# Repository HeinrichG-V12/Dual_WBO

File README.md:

# Dual channel wideband oxygen controller

## Development status

- Hardware: working in progress, check hardware/V0.0.1 for actual status
- Software: not started yet

### Dual WBO controller based on

- Microchip AT90CAN128
- 2x Bosch CJ125 wideband lambda controller
- NXP TJA1050T high speed can transceiver
- Infineon TLE42754D LDO 5v and 450mA
- Analog Devices AD5337 8-bit DAC
- Analog Devices ADR02 5v and 10mA precision reference (0.1%) for TLS115
- Infineon TLS115B0EJ voltage tracker for analog part, provides 5v and 150mA
- ...

### Features

- supports **LSU4.9** probes only
- Automotive grade components
- 2x LSU 4.9 connector (TE 1813139-1)
- 4 layer PCB
- integrated with TunerStudio

### Inputs

- 2x LSU4.9 probes
- CAN HS with up to 1mbit/s
- UART for configuration
- UBat input for activation the controller

### Outputs

- dual analog output, either as 0..5V for Lambda 0.65 to 1.35 **OR** narrow band emulation
- CAN output (AEM X-Series protocol) for both channels and debug messages

### Bosch CJ125 (LQFP32 package) part numbers

|Bosch part number|
|:----------------|
|30615|
|40103|
|30522|

#### A couple of CJ125 ICs

### Suitable Bosch lambda probes

Basically, the Bosch probes whose numbers start with **0 258 017** will fit, also Bosch **0 281 004**.  
Bosch numbers beginning with **0 258 007** are *LSU 4.2* probes and will not fit.

|Bosch number  |Length overall|Comment|
|--------------|--------------|-------|
|0 258 017 012 |1060mm||
|0 258 017 025 |1000mm|Bosch motorsport part|
|0 258 017 029 |620mm|grey, used by BMW after 09/2006 (1178 7539124)|
|0 258 017 038 |340mm|grey, used by BMW (11787537984)|
|0 258 017 092 |950mm|black, used by BMW (1178 7540167)|
|0 258 017 126 |680mm|black, used by BMW after 09/2006 (1178 7561410)|
|0 281 004 028 |540mm||
|0 281 004 150 |1215mm||
|0 281 004 184 |1000mm||
|...|||

### LSU4.9 probe pinout

|Pin#|Color|Description|Symbol|
|----|-----|--------|-----------|
|1|red|Pump current APE|IP|
|2|yellow|Virtual ground IPN|VM|
|3|white|Heater voltage H-|Uh-|
|4|grey|Heater voltaget H+|Uh+|
|5|green|Trim Resistor RT|IA|
|6|black|Nernst voltage UN|RE|

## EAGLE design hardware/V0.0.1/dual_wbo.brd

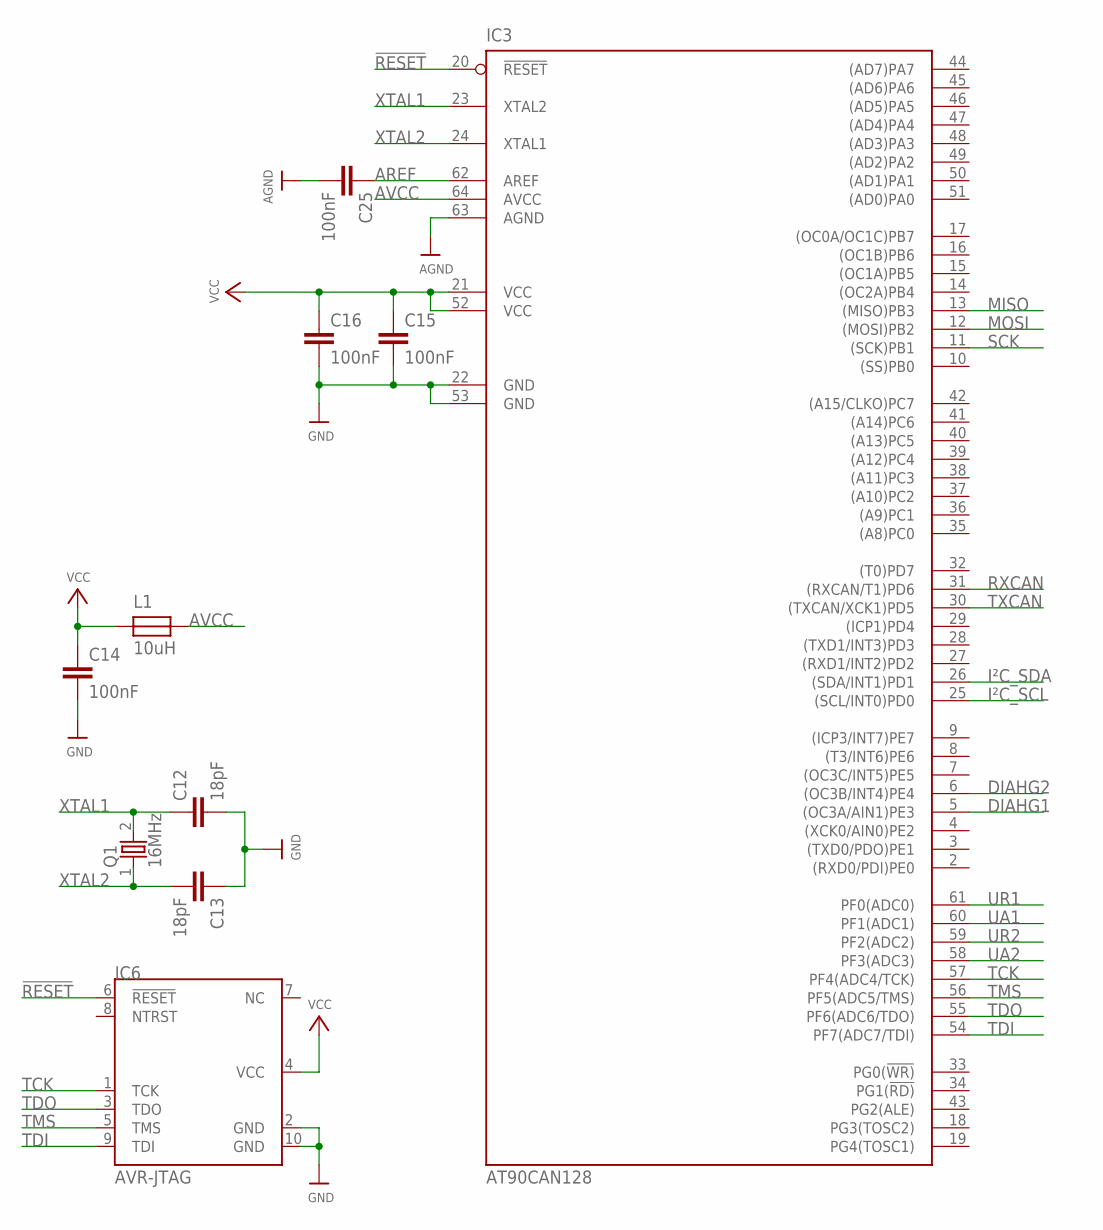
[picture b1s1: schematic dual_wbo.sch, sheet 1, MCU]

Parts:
C12, C13: 18pF; C0603
C14, C15, C16, C25: 100nF; C0603
IC3: AT90CAN128; TQFP64
IC6: AVR-JTAG; 2X05_1.27MM_SMT
L1: 10uH; R0603
Q1: 16MHz; ABM3

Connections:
!RESET: IC3.20 (!RESET), IC6.6 (!RESET)
AGND: C25.2, IC3.63 (AGND); also elsewhere on the board
AREF: C25.1, IC3.62 (AREF); also elsewhere on the board
AVCC: IC3.64 (AVCC), L1.2
DIAHG1: IC3.5 ((OC3A/AIN1)PE3); also elsewhere on the board
DIAHG2: IC3.6 ((OC3B/INT4)PE4); also elsewhere on the board
GND: C12.2, C13.1, C14.2, C15.2, C16.2, IC3.22 (GND), IC3.53 (GND), IC6.2 (GND), IC6.10 (GND); also elsewhere on the board
I²C_SCL: IC3.25 ((SCL/INT0)PD0); also elsewhere on the board
I²C_SDA: IC3.26 ((SDA/INT1)PD1); also elsewhere on the board
MISO: IC3.13 ((MISO)PB3); also elsewhere on the board
MOSI: IC3.12 ((MOSI)PB2); also elsewhere on the board
RXCAN: IC3.31 ((RXCAN/T1)PD6); also elsewhere on the board
SCK: IC3.11 ((SCK)PB1); also elsewhere on the board
TCK: IC3.57 (PF4(ADC4/TCK)), IC6.1 (TCK)
TDI: IC3.54 (PF7(ADC7/TDI)), IC6.9 (TDI)
TDO: IC3.55 (PF6(ADC6/TDO)), IC6.3 (TDO)
TMS: IC3.56 (PF5(ADC5/TMS)), IC6.5 (TMS)
TXCAN: IC3.30 ((TXCAN/XCK1)PD5); also elsewhere on the board
UA1: IC3.60 (PF1(ADC1)); also elsewhere on the board
UA2: IC3.58 (PF3(ADC3)); also elsewhere on the board
UR1: IC3.61 (PF0(ADC0)); also elsewhere on the board
UR2: IC3.59 (PF2(ADC2)); also elsewhere on the board
VCC: C14.1, C15.1, C16.1, IC3.21 (VCC), IC3.52 (VCC), IC6.4 (VCC), L1.1; also elsewhere on the board
XTAL1: C12.1, IC3.23 (XTAL2), Q1.2
XTAL2: C13.2, IC3.24 (XTAL1), Q1.1

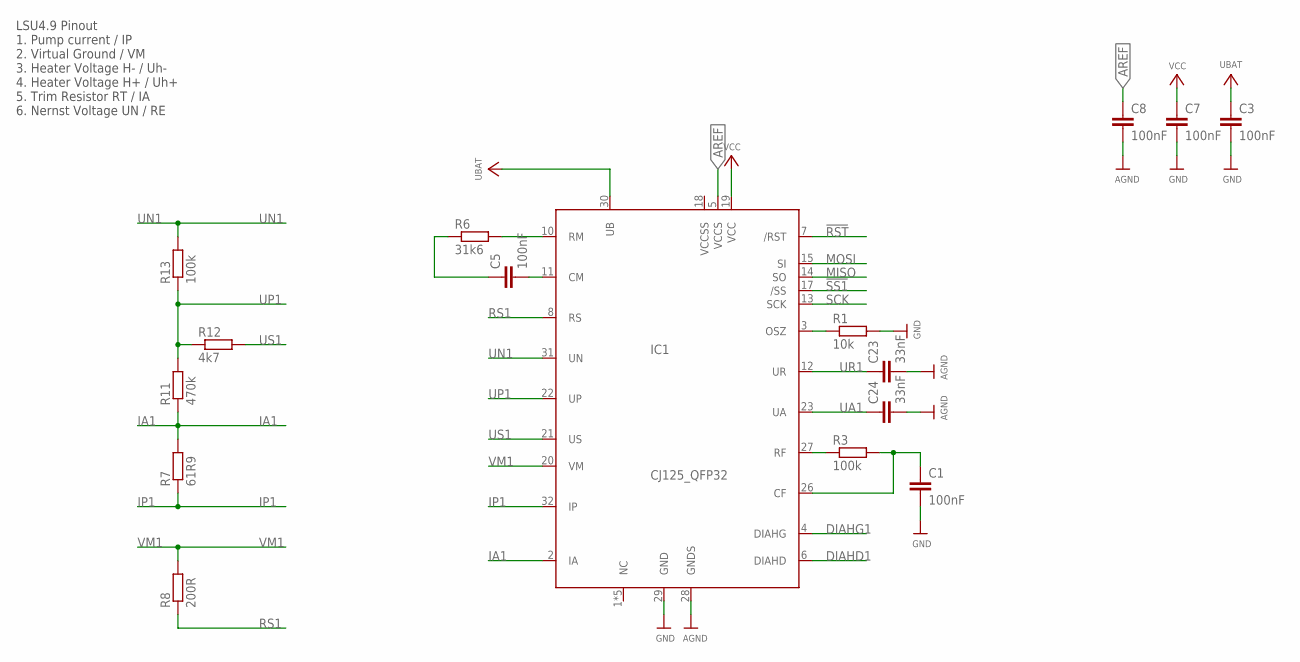
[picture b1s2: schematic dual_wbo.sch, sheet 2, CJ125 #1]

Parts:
C1, C3, C5, C7, C8: 100nF; C0603
C23, C24: 33nF; C0603
IC1: CJ125_QFP32; TQFP32-08
R1: 10k; R0603
R3, R13: 100k; R0603
R6: 31k6; R0603
R7: 61R9; R0603
R8: 200R; R0603
R11: 470k; R0603
R12: 4k7; R0603

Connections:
!RST: IC1.7 (/RST); also elsewhere on the board
!SS1: IC1.17 (/SS)
+UBAT: C3.1, IC1.30 (UB); also elsewhere on the board
AGND: C8.2, C23.2, C24.2, IC1.28 (GNDS); also elsewhere on the board
AREF: C8.1, IC1.5 (VCCS); also elsewhere on the board
DIAHD1: IC1.6 (DIAHD); also elsewhere on the board
DIAHG1: IC1.4 (DIAHG); also elsewhere on the board
GND: C1.2, C3.2, C7.2, IC1.29 (GND), R1.2; also elsewhere on the board
IA1: IC1.2 (IA), R7.2, R11.1
IP1: IC1.32 (IP), R7.1
MISO: IC1.14 (SO); also elsewhere on the board
MOSI: IC1.15 (SI); also elsewhere on the board
unnamed: IC1.3 (OSZ), R1.1
unnamed: IC1.27 (RF), R3.1
unnamed: C1.1, IC1.26 (CF), R3.2
unnamed: IC1.10 (RM), R6.2
unnamed: C5.1, R6.1
unnamed: C5.2, IC1.11 (CM)
RS1: IC1.8 (RS), R8.1
SCK: IC1.13 (SCK); also elsewhere on the board
UA1: C24.1, IC1.23 (UA); also elsewhere on the board
UN1: IC1.31 (UN), R13.2
UP1: IC1.22 (UP), R11.2, R12.1, R13.1
UR1: C23.1, IC1.12 (UR); also elsewhere on the board
US1: IC1.21 (US), R12.2
VCC: C7.1, IC1.19 (VCC); also elsewhere on the board
VM1: IC1.20 (VM), R8.2

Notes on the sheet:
LSU4.9 Pinout 1. Pump current / IP 2. Virtual Ground / VM 3. Heater Voltage H- / Uh- 4. Heater Voltage H+ / Uh+ 5. Trim Resistor RT / IA 6. Nernst Voltage UN / RE

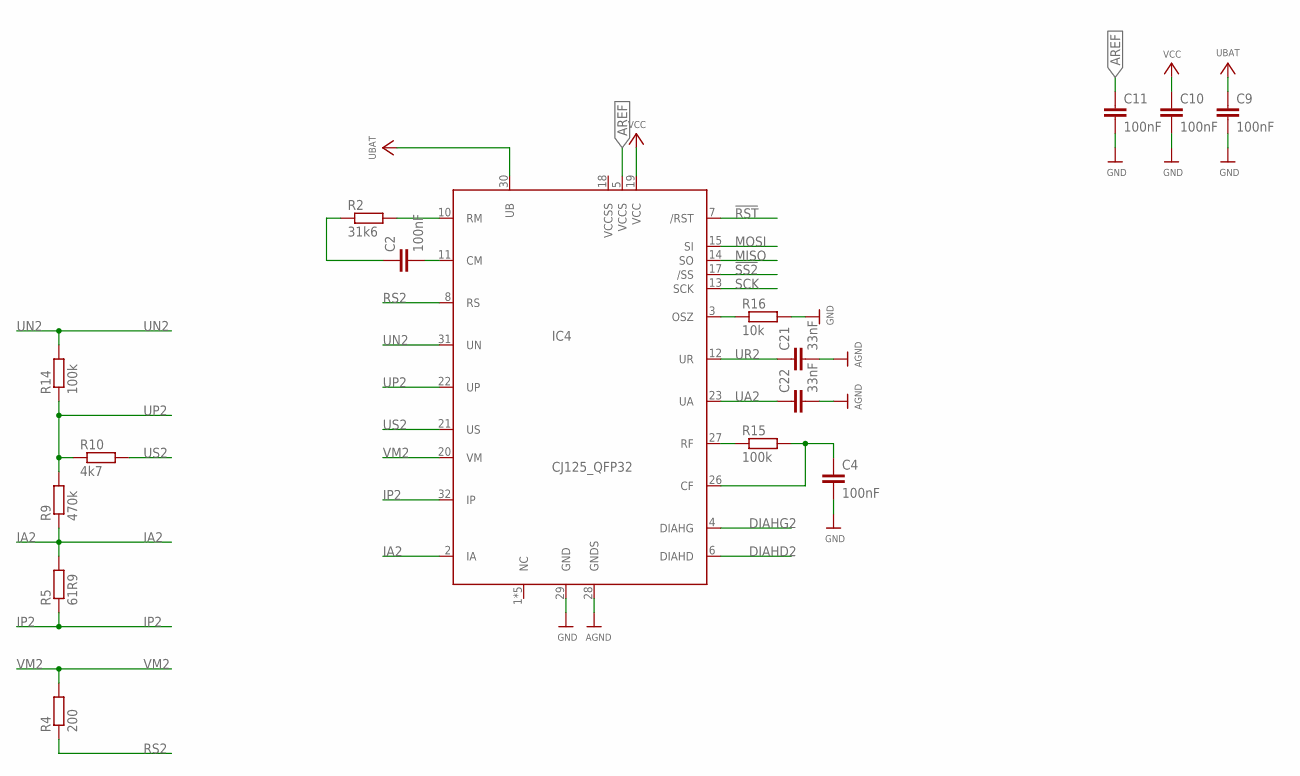
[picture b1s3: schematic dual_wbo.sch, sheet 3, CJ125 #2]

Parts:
C2, C4, C9, C10, C11: 100nF; C0603
C21, C22: 33nF; C0603
IC4: CJ125_QFP32; TQFP32-08
R2: 31k6; R0603
R4: 200; R0603
R5: 61R9; R0603
R9: 470k; R0603
R10: 4k7; R0603
R14, R15: 100k; R0603
R16: 10k; R0603

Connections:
!RST: IC4.7 (/RST); also elsewhere on the board
!SS2: IC4.17 (/SS)
AGND: C21.2, C22.2, IC4.28 (GNDS); also elsewhere on the board
AREF: C11.1, IC4.5 (VCCS); also elsewhere on the board
DIAHD2: IC4.6 (DIAHD); also elsewhere on the board
DIAHG2: IC4.4 (DIAHG); also elsewhere on the board
GND: C4.2, C9.2, C10.2, C11.2, IC4.29 (GND), R16.2; also elsewhere on the board
IA2: IC4.2 (IA), R5.2, R9.1
IP2: IC4.32 (IP), R5.1
MISO: IC4.14 (SO); also elsewhere on the board
MOSI: IC4.15 (SI); also elsewhere on the board
unnamed: C2.1, R2.1
unnamed: IC4.27 (RF), R15.1
unnamed: C4.1, IC4.26 (CF), R15.2
unnamed: C2.2, IC4.11 (CM)
unnamed: IC4.10 (RM), R2.2
unnamed: IC4.3 (OSZ), R16.1
RS2: IC4.8 (RS), R4.1
SCK: IC4.13 (SCK); also elsewhere on the board
UA2: C22.1, IC4.23 (UA); also elsewhere on the board
UN2: IC4.31 (UN), R14.2
UP2: IC4.22 (UP), R9.2, R10.1, R14.1
UR2: C21.1, IC4.12 (UR); also elsewhere on the board
US2: IC4.21 (US), R10.2
VBAT: C9.1, IC4.30 (UB)
VCC: C10.1, IC4.19 (VCC); also elsewhere on the board
VM2: IC4.20 (VM), R4.2

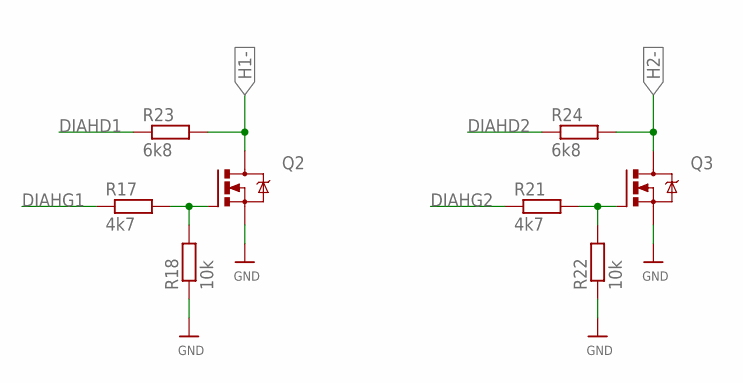
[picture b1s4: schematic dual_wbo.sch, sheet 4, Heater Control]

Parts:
Q2, Q3: N_MOSFETTO252; TO252
R17, R21: 4k7; R0603
R18, R22: 10k; R0603
R23, R24: 6k8; R0603

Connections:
DIAHD1: R23.1; also elsewhere on the board
DIAHD2: R24.1; also elsewhere on the board
DIAHG1: R17.1; also elsewhere on the board
DIAHG2: R21.1; also elsewhere on the board
GND: Q2.3 (S), Q3.3 (S), R18.1, R22.1; also elsewhere on the board
H1-: Q2.2 (D), R23.2
H2-: Q3.2 (D), R24.2
unnamed: Q2.1 (G), R17.2, R18.2
unnamed: Q3.1 (G), R21.2, R22.2

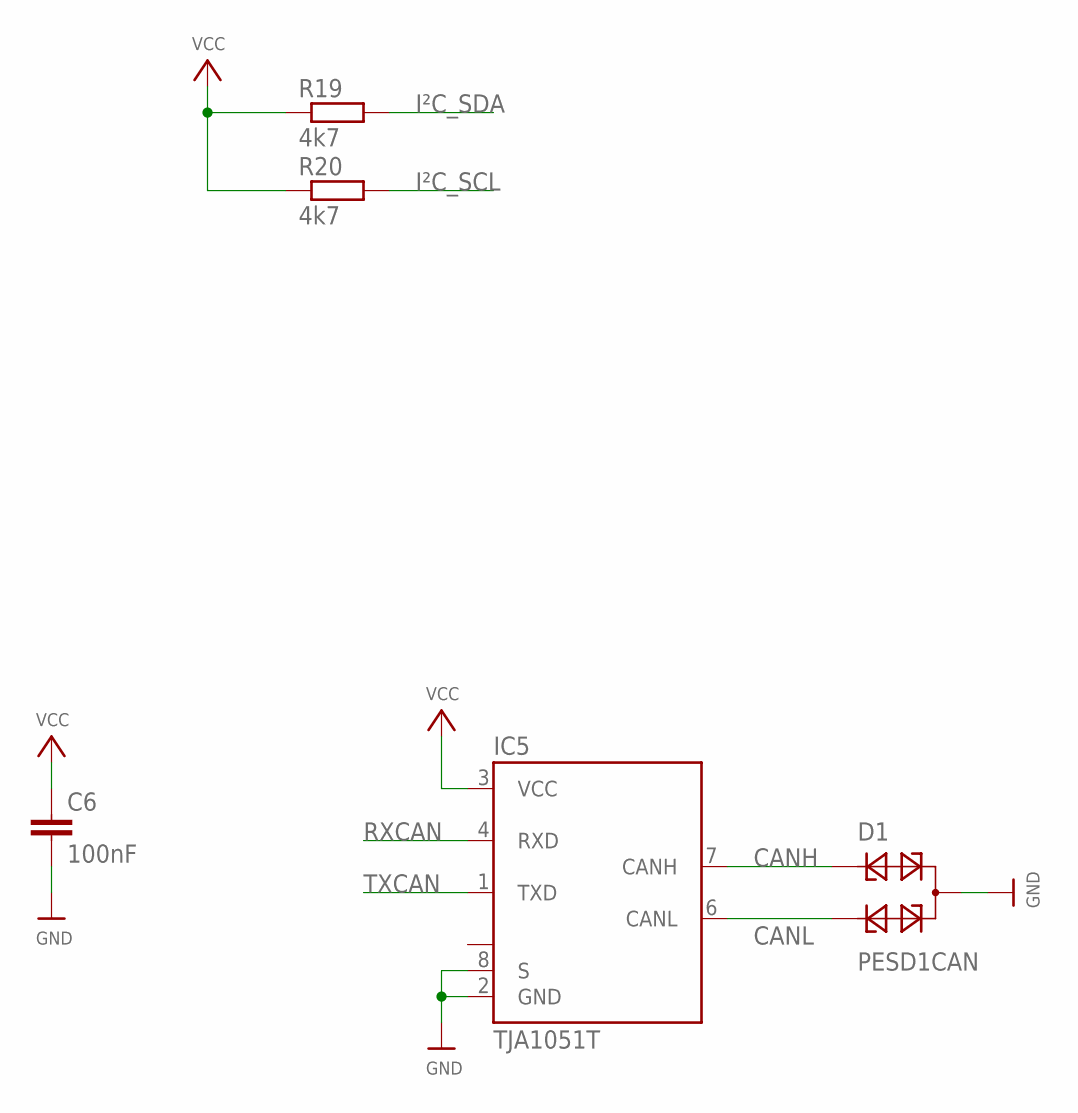
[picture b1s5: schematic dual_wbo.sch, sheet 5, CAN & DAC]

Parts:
C6: 100nF; C0603
D1: PESD1CAN; SOT23
IC5: TJA1051T; SO8
R19, R20: 4k7; R0603

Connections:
CANH: D1.1, IC5.7 (CANH)
CANL: D1.2, IC5.6 (CANL)
GND: C6.2, D1.3, IC5.2 (GND), IC5.8 (S); also elsewhere on the board
I²C_SCL: R20.2; also elsewhere on the board
I²C_SDA: R19.2; also elsewhere on the board
RXCAN: IC5.4 (RXD); also elsewhere on the board
TXCAN: IC5.1 (TXD); also elsewhere on the board
VCC: C6.1, IC5.3 (VCC), R19.1, R20.1; also elsewhere on the board

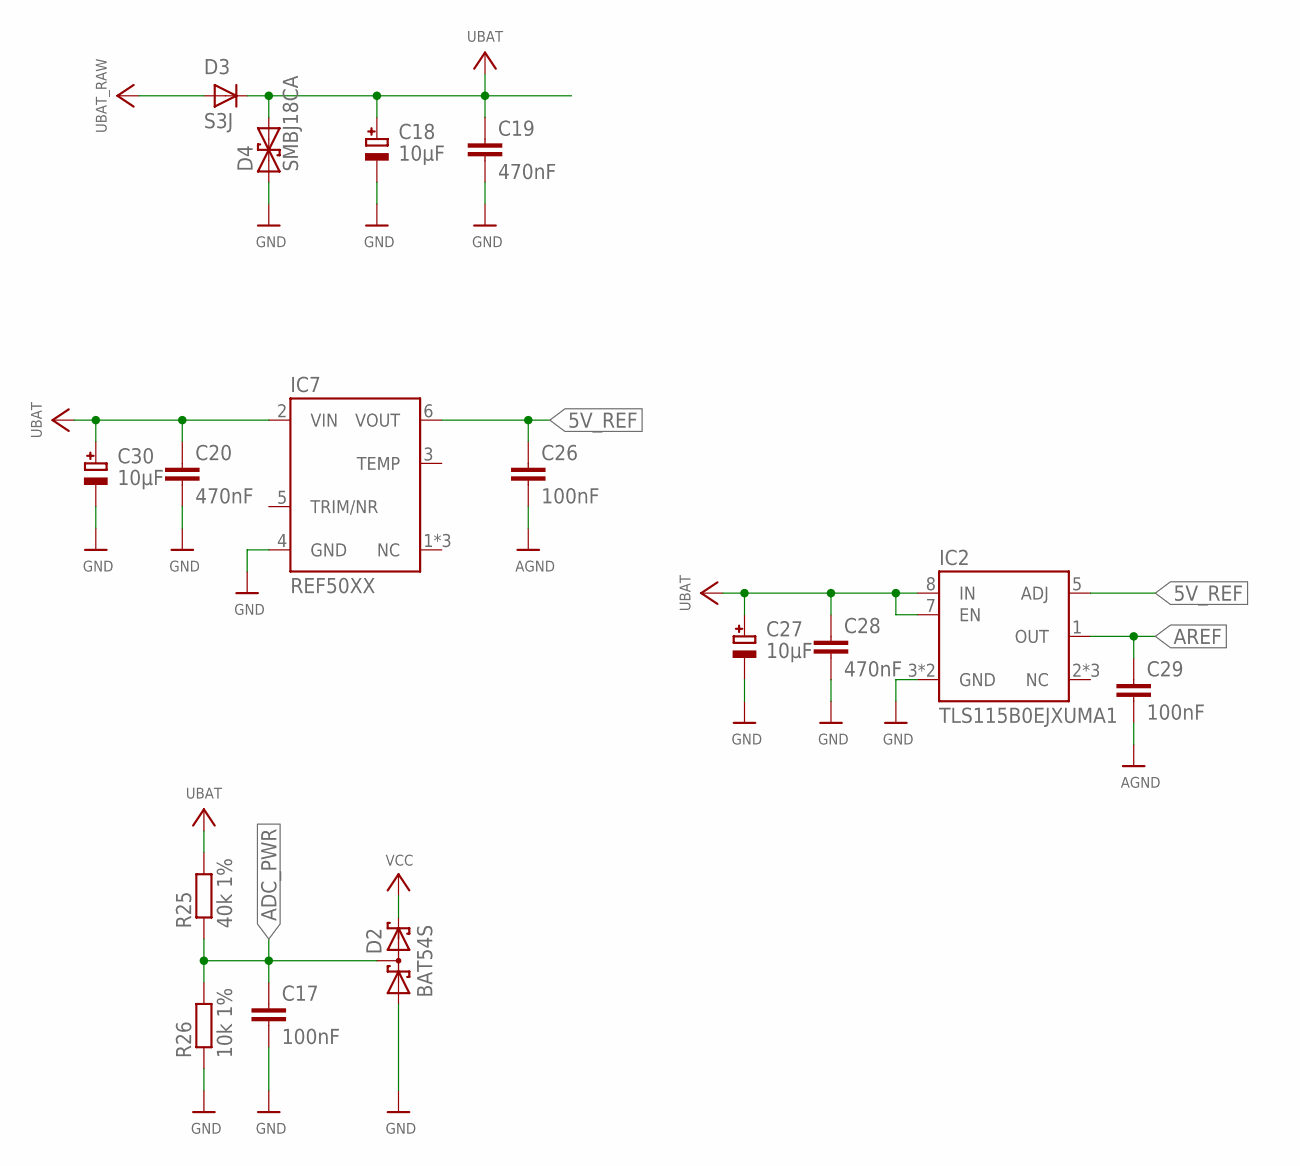
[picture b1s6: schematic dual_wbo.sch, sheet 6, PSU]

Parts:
C17, C26, C29: 100nF; C0603
C18, C27, C30: 10µF; SMC_C
C19: 470nF; C0805
C20, C28: 470nF; C0603
D2: BAT54S; SOT23
D3: S3J; SMB
D4: SMBJ18CA; DO214AA
IC2: TLS115B0EJXUMA1; SOIC127P600X170-9N
IC7: REF50XX; SOIC127P600X175-8N
R25: 40k 1%; R0603
R26: 10k 1%; R0603

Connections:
5V_REF: C26.1, IC2.5 (ADJ), IC7.6 (VOUT)
+UBAT: C18.+, C19.1, C20.1, C27.+, C28.1, C30.+, D3.A (C), D3.C (A), D4.C (2), IC2.7 (EN), IC2.8 (IN), IC7.2 (VIN), R25.2; also elsewhere on the board
ADC_PWR: C17.1, D2.3 (C1A2), R25.1, R26.2
AGND: C26.2, C29.2; also elsewhere on the board
AREF: C29.1, IC2.1 (OUT); also elsewhere on the board
GND: C17.2, C18.-, C19.2, C20.2, C27.-, C28.2, C30.-, D2.1 (A1), D4.A (1), IC2.3 (GND), IC2.9 (GND), IC7.4 (GND), R26.1; also elsewhere on the board
VCC: D2.2 (C2); also elsewhere on the board

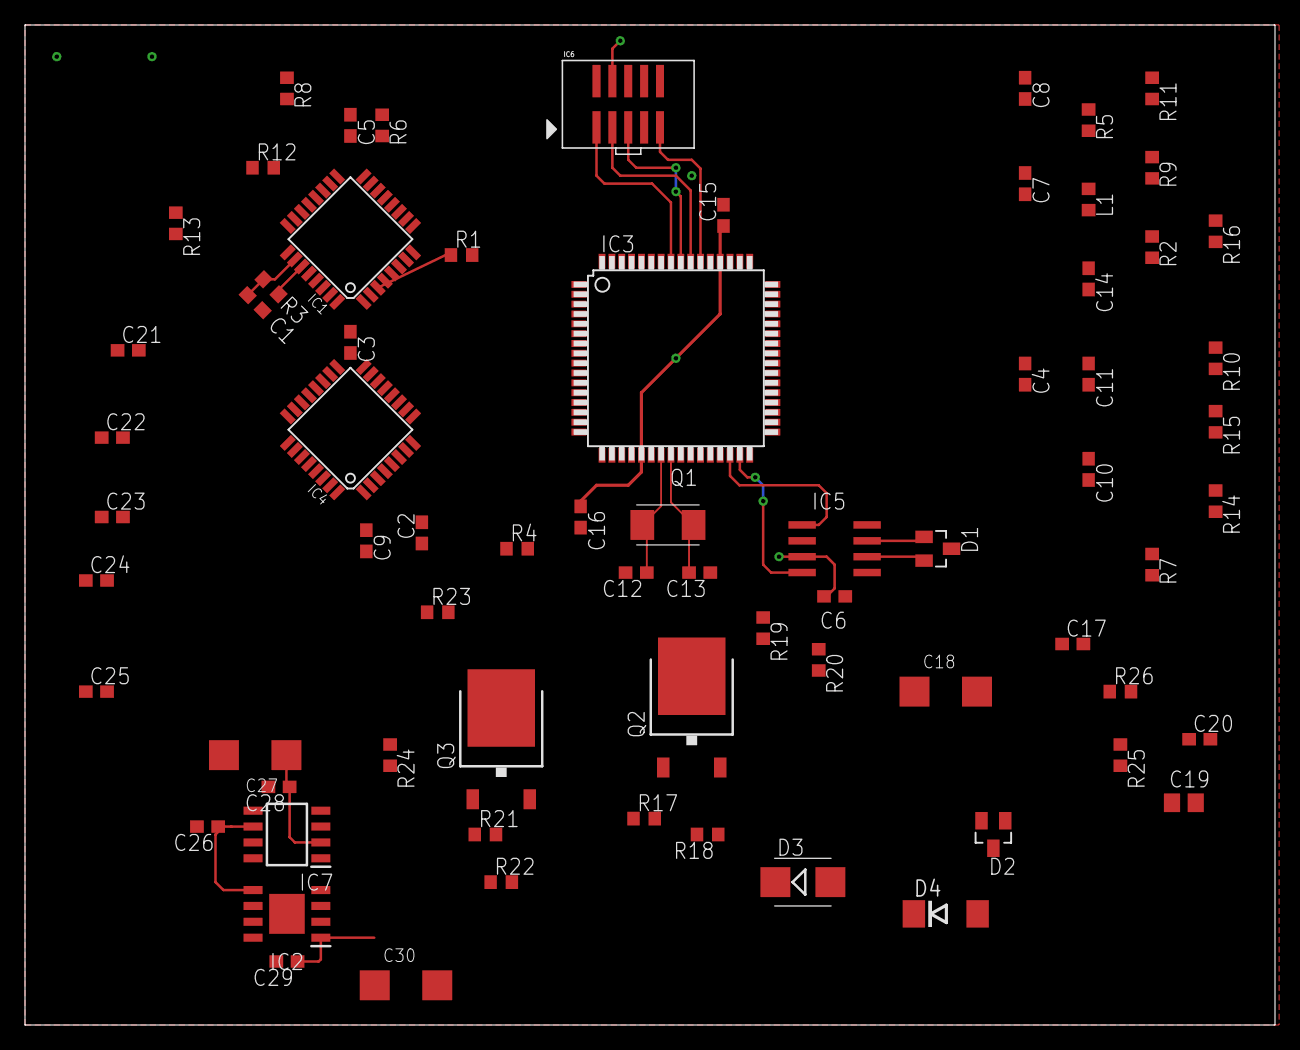
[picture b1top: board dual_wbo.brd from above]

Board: 4 copper layers, 100.0 x 80.0 mm, 71 parts (0 on the bottom side), 64 nets.

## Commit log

2021-12-01 .gitignore added
2021-12-01 readme modified
2021-12-01 readme modified, empty software project created
2021-12-06 bosch probes added
2021-12-10 some infos added
2021-12-11 -> some data sheets added -> added eagle files in hardware/V0.0.1 -> readme.md modified
2021-12-12 -> dac name corrected -> dac datasheet added
2021-12-12 Software removed, restart
2021-12-12 Start new software
2021-12-14 some changes
2021-12-14 Schematic updated
2022-02-16 lsu 4.9 connector erder number added
2022-02-16 dbc file for aemnet x-series added
2022-05-03 test erstellt
2022-05-03 test.txt deleted
2022-05-03 some basic stuff
2022-05-03 can basics
2022-05-03 pwm basics
2022-05-03 pid basics
2022-05-03 uart buffer basics
2022-05-03 test
2022-05-05 ini file extended
2022-05-05 a lot of modifications
2022-05-05 ini file corrected
2022-05-11 some changes in ini
2022-05-12 initial import TS_Test project to git
2022-05-18 ini file corrected and extended, added curve editor
2022-05-18 calculation algorithm removed
2022-05-18 commented
2022-05-18 help link changed
2022-05-18 some helper functions
2022-05-19 pump current calculation added, lambda calculation added, some change
2022-09-09 lsu probes description
2023-01-25 c++ project started

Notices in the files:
parts and their libraries:
microbuilder: This work is placed in the public domain, and may be freely used for commercial and non-commercial work with the following conditions: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
